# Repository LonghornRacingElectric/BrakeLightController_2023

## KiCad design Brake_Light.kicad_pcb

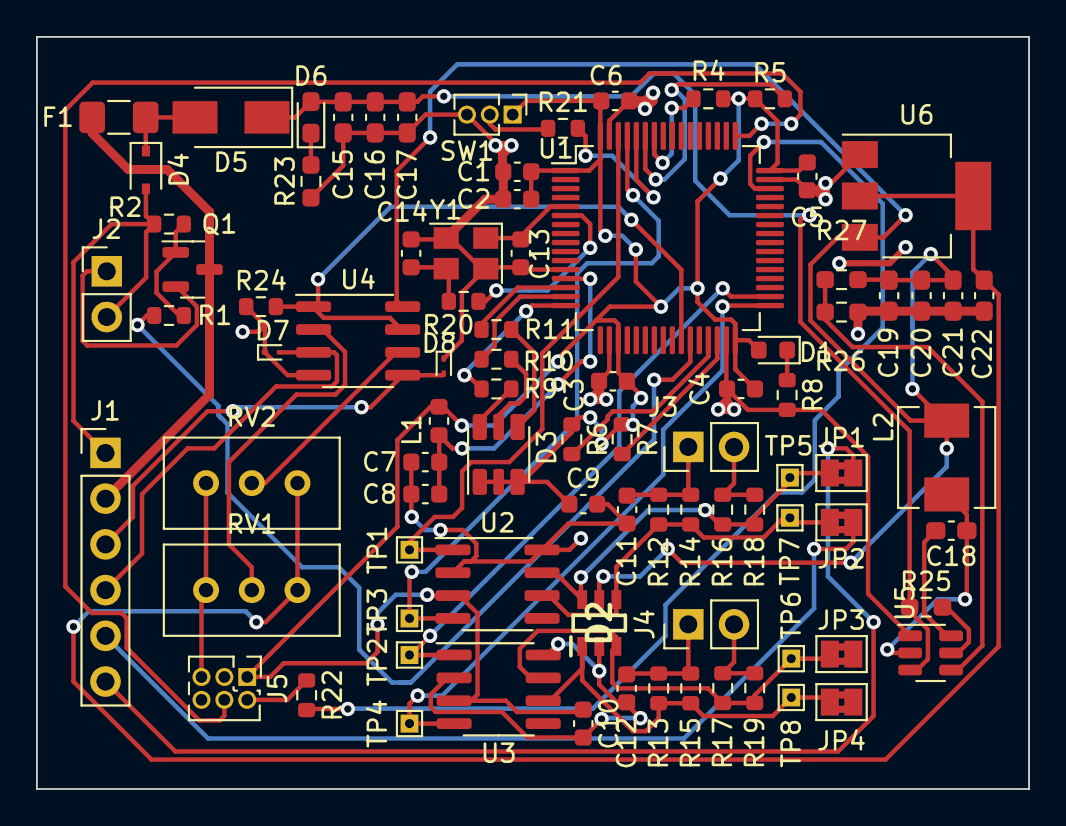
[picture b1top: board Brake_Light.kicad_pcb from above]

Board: 2 copper layers, 55.1 x 41.8 mm, 88 parts (1 on the bottom side), 54 nets.

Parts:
 : LOGO
C1: 4u7; C_0603_1608Metric
C2, C3, C4, C5, C6: 100n; C_0603_1608Metric
C7: 1u; C_0603_1608Metric
C8: 10n; C_0603_1608Metric
C9, C10: 0u1; C_0603_1608Metric
C11, C12: 4.7n; C_0603_1608Metric
C13, C14: 10p; C_0603_1608Metric
C15, C16: 10uF; C_0603_1608Metric_Pad1.08x0.95mm_HandSolder
C17, C18: 100nF; C_0603_1608Metric_Pad1.08x0.95mm_HandSolder
C19, C20, C22: 22uF; C_0603_1608Metric_Pad1.08x0.95mm_HandSolder
C21: 1uF; C_0603_1608Metric_Pad1.08x0.95mm_HandSolder
D1: RED; LED_0603_1608Metric
D2: DT1446-04TS-7; SOT95P280X100-6N
D3: SMLVN6RGB; LED_ROHM_SMLVN6
D4: 32V; D_SOD-323
D5: 0.7dV; D_SMA
D6: LED; LED_0603_1608Metric_Pad1.05x0.95mm_HandSolder
D7, D8: D_TVS; D_SOD-923
F1: 2A; Fuse_1206_3216Metric_Pad1.42x1.75mm_HandSolder
J1: Conn_01x06; PinHeader_1x06_P2.54mm_Vertical
J2, J3, J4: Conn_01x02; PinHeader_1x02_P2.54mm_Vertical
J5: SWD; PinHeader_2x03_P1.27mm_Vertical
JP1, JP2, JP3, JP4: SolderJumper-2_P1.3mm_Bridged2Bar_Pad1.0x1.5mm
L1: 68n; L_0603_1608Metric
L2: 4u7; L_Sunlord_MWSA0518_5.4x5.2mm
Q1: AO3400A; SOT-23
R1: 2k; R_0603_1608Metric
R2: 1k5; R_0603_1608Metric
R4, R5, R6, R7: 2k2; R_0603_1608Metric
R8: 100; R_0603_1608Metric
R9, R10, R11: 220; R_0603_1608Metric
R12, R13, R14, R15, R16, R17, R18, R19: 120; R_0603_1608Metric
R20: 47; R_0603_1608Metric
R21: 10K; R_0603_1608Metric
R22: 22; R_0603_1608Metric
R23: 470R; R_0603_1608Metric_Pad0.98x0.95mm_HandSolder
R24: 10k; R_0603_1608Metric
R25, R26: 10K; R_0603_1608Metric_Pad0.98x0.95mm_HandSolder
R27: 54.9K; R_0603_1608Metric_Pad0.98x0.95mm_HandSolder
RV1, RV2: R_Potentiometer_Trim; Potentiometer_Bourns_3296W_Vertical
SW1: SW_SPDT; PinHeader_1x03_P1.27mm_Vertical
TP1, TP2, TP3, TP4, TP5, TP6, TP7, TP8: TestPoint_THTPad_1.0x1.0mm_Drill0.5mm
U1: STM32F105RCTx; LQFP-64_10x10mm_P0.5mm
U2, U3: SN65HVD230; SOIC-8_3.9x4.9mm_P1.27mm
U4: LM393; SOIC-8_3.9x4.9mm_P1.27mm
U5: LMR51420; SOT-23-6
U6: AMS1117-3.3; SOT-223-3_TabPin2
Y1: 16MHz; Crystal_SMD_3225-4Pin_3.2x2.5mm

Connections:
+3.3V: C1.1, C2.1, C3.1, C4.1, C5.1, C6.1, C9.1, C10.1, D1.2 (A), D3.1 (BA), D3.2 (RA), D3.3 (GA), J5.1, L1.1, R4.1, R5.1, R6.1, R7.1, SW1.1 (A), U1.1 (VBAT), U1.19 (VDD), U1.32 (VDD), U1.48 (VDD), U1.64 (VDD), U2.3 (VCC), U3.3 (VCC)
+3.3VA: C7.1, C8.1, L1.2, U1.13 (VDDA)
+3V3: C22.1, RV1.1, RV2.1, U6.2 (VO)
+5V: C19.1, C20.1, C21.1, D2.5 (VCC), L2.2, R27.2, U4.8 (V+), U6.3 (VI)
+24V: F1.2, J1.2, Q1.3 (D)
/Brake1: D7.2 (A2), J1.4, U4.3 (+)
/Brake2: D8.2 (A2), J1.3, U4.5 (+)
/Brake_Output: R1.1, U1.27 (PB1)
/Brake_Signal: R24.2, U1.26 (PB0), U4.1, U4.7
/CANH: J1.6, JP1.2 (B)
/CANL: J1.5, JP2.2 (B)
/Microcontroller/BOOT0: R21.2, U1.60 (BOOT0)
/Microcontroller/CAN1_RX: TP3.1, U1.61 (PB8), U2.4 (R)
/Microcontroller/CAN1_TX: TP1.1, U1.62 (PB9), U2.1 (D)
/Microcontroller/CAN2_RX: TP4.1, U1.33 (PB12), U3.4 (R)
/Microcontroller/CAN2_TX: TP2.1, U1.34 (PB13), U3.1 (D)
/Microcontroller/HSE_in: C13.1, U1.5 (PD0), Y1.1
/Microcontroller/HSE_out: R20.1, U1.6 (PD1)
/Microcontroller/I2C1_SCL: R4.2, U1.58 (PB6)
/Microcontroller/I2C1_SDA: R5.2, U1.59 (PB7)
/Microcontroller/I2C2_SCL: R6.2, U1.29 (PB10)
/Microcontroller/I2C2_SDA: R7.2, U1.30 (PB11)
/Microcontroller/LED_B: R9.2, U1.16 (PA2)
/Microcontroller/LED_G: R10.2, U1.15 (PA1)
/Microcontroller/LED_R: R11.2, U1.14 (PA0)
/Microcontroller/SWCLK: J5.4, U1.49 (PA14)
/Microcontroller/SWDIO: R22.2, U1.46 (PA13)
/StandardizedVRMS/BUCK/EN: R25.2, U5.5 (EN)
/StandardizedVRMS/BUCK/SW: C18.1, L2.1, U5.2 (SW)
/StandardizedVRMS/BUCK/VBST: C18.2, U5.6 (VBST)
/StandardizedVRMS/BUCK/VFB: R26.1, R27.1, U5.4 (VFB)
/StandardizedVRMS/BUCK/V_in: C15.1, C16.1, C17.1, D5.1 (K), D6.2 (A), R25.1, U5.3 (VIN)
/StandardizedVRMS/DIODE: D4.1 (K), D5.2 (A), F1.1
GND: C1.2, C2.2, C3.2, C4.2, C5.2, C6.2, C7.2, C8.2, C9.2, C10.2, C11.1, C12.1, C13.2, C14.2, C15.2, C16.2, C17.2, C19.2, C20.2, C21.2, C22.2, D2.2 (VSS), D4.2 (A), D7.1 (A1), D8.1 (A1), J1.1, J2.2, J5.5, R2.2, R8.2, R23.1, R24.1, R26.2, RV1.3, RV2.3, SW1.3 (C), U1.12 (VSSA), U1.18 (VSS), U1.31 (VSS), U1.47 (VSS), U1.63 (VSS), U2.2 (GND), U2.8 (Rs), U3.2 (GND), U3.8 (Rs), U4.4 (V-), U5.1 (GND), U6.1 (GND), Y1.2, Y1.4
unnamed: C11.2, J3.1, R12.1, R14.1
unnamed: C12.2, J4.1, R13.1, R15.1
unnamed: C14.1, R20.2, Y1.3
unnamed: D1.1 (K), R8.1
unnamed: D2.1 (I/O1), JP4.1 (A), R13.2, R15.2, TP8.1, U3.6 (CANL)
unnamed: D2.3 (I/O2), JP3.1 (A), R17.1, R19.1, TP6.1, U3.7 (CANH)
unnamed: D2.4 (I/O3), JP2.1 (A), R12.2, R14.2, TP7.1, U2.6 (CANL)
unnamed: D2.6 (I/O4), JP1.1 (A), R16.1, R18.1, TP5.1, U2.7 (CANH)
unnamed: D3.4 (GK), R11.1
unnamed: D3.5 (RK), R10.1
unnamed: D3.6 (BK), R9.1
unnamed: D6.1 (K), R23.2
unnamed: J2.1, Q1.2 (S)
unnamed: J3.2, R16.2, R18.2
unnamed: J4.2, R17.2, R19.2
unnamed: J5.2, R22.1
unnamed: Q1.1 (G), R1.2, R2.1
unnamed: R21.1, SW1.2 (B)
unnamed: RV1.2, U4.2 (-)
unnamed: RV2.2, U4.6 (-)

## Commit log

2022-09-26 Added 2023KicadLibrary
2022-10-31 updated brake light
2022-10-31 fixed version control
2022-11-07 completed initial schematic
2022-11-13 post revision 1
2022-11-14 finalized
2022-12-17 layout
2022-12-27 updated kicadlibrary and added void space under crystal
2023-01-09 finished layout
